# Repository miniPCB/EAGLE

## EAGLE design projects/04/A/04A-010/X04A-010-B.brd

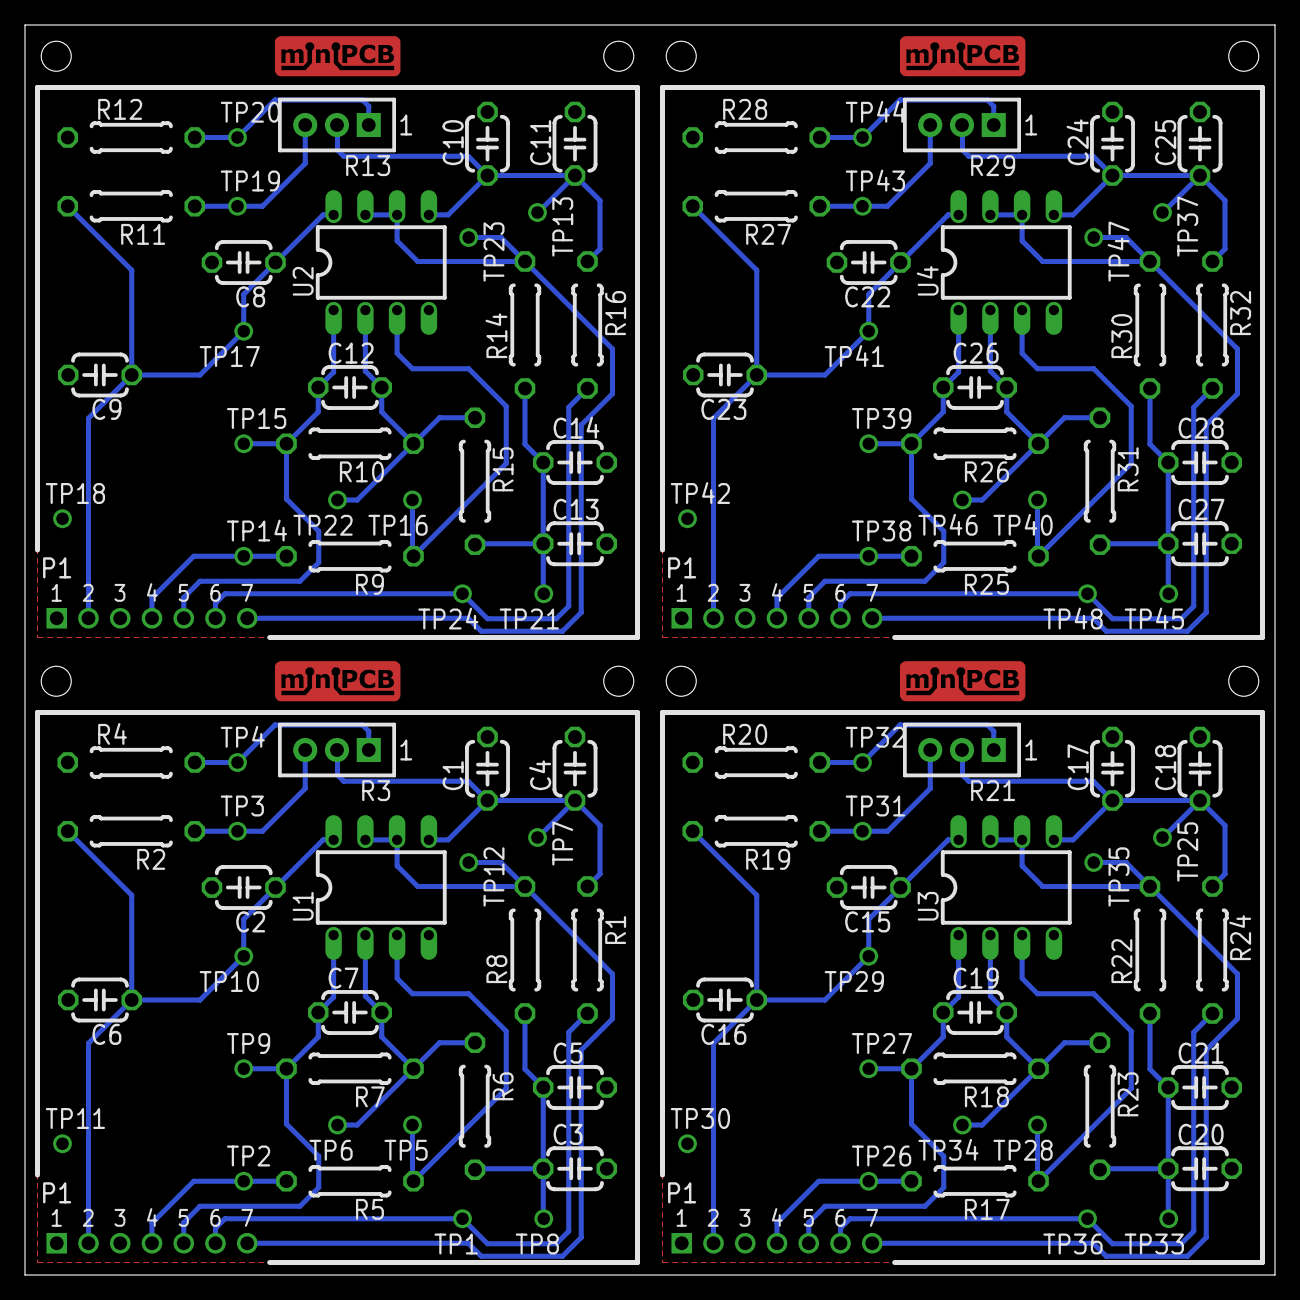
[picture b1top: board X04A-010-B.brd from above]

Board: 2 copper layers, 100.0 x 100.0 mm, 117 parts (0 on the bottom side), 48 nets.

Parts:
C1, C2, C3, C4, C5, C6, C7, C8, C9, C10, C11, C12, C13, C14, C15, C16, C17, C18, C19, C20, C21, C22, C23, C24, C25, C26, C27, C28: C050-024X044
E$1: MINIPCB_PANEL_IMAGEFRAME
P1-, P1-1, P1-2, P1-3: MINIPCB_7P_50X50
R1, R2, R4, R5, R6, R7, R8, R9, R10, R11, R12, R14, R15, R16, R17, R18, R19, R20, R22, R23, R24, R25, R26, R27, R28, R30, R31, R32: 0207/10
R3, R13, R21, R29: TRIM_0100
TP1, TP2, TP3, TP4, TP5, TP6, TP7, TP8, TP9, TP10, TP11, TP12, TP13, TP14, TP15, TP16, TP17, TP18, TP19, TP20, TP21, TP22, TP23, TP24, TP25, TP26, TP27, TP28, TP29, TP30, TP31, TP32, TP33, TP34, TP35, TP36, TP37, TP38, TP39, TP40, TP41, TP42, TP43, TP44, TP45, TP46, TP47, TP48: PINS_1_TESTPOINT_KE5000_NOTEXT
U1, U2, U3, U4: DIL08

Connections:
BIAS: C1.1, C4.1, R1.1, R3.2, TP7.1, U1.5
BIAS1: C10.1, C11.1, R13.2, R16.1, TP13.1, U2.5
BIAS2: C17.1, C18.1, R21.2, R24.1, TP25.1, U3.5
BIAS3: C24.1, C25.1, R29.2, R32.1, TP37.1, U4.5
BIAS_CONTROL: P1-.6, R1.2, TP1.1
BIAS_CONTROL1: P1-1.6, R16.2, TP24.1
BIAS_CONTROL2: P1-2.6, R24.2, TP36.1
BIAS_CONTROL3: P1-3.6, R32.2, TP48.1
GND: C1.2, C2.2, C3.2, C4.2, C5.2, C6.2, P1-.1, R4.1, TP11.1, U1.4
GND1: C8.2, C9.2, C10.2, C11.2, C13.2, C14.2, P1-1.1, R12.1, TP18.1, U2.4
GND2: C15.2, C16.2, C17.2, C18.2, C20.2, C21.2, P1-2.1, R20.1, TP30.1, U3.4
GND3: C22.2, C23.2, C24.2, C25.2, C27.2, C28.2, P1-3.1, R28.1, TP42.1, U4.4
IN: P1-.4, R5.2, TP2.1
IN1: P1-1.4, R9.2, TP14.1
IN2: P1-2.4, R17.2, TP26.1
IN3: P1-3.4, R25.2, TP38.1
IN+: R5.1, TP5.1, U1.3
IN+1: R9.1, TP16.1, U2.3
IN+2: R17.1, TP28.1, U3.3
IN+3: R25.1, TP40.1, U4.3
OUT: C7.1, P1-.5, R7.2, TP9.1, U1.1
OUT1: C12.1, P1-1.5, R10.2, TP15.1, U2.1
OUT2: C19.1, P1-2.5, R18.2, TP27.1, U3.1
OUT3: C26.1, P1-3.5, R26.2, TP39.1, U4.1
POT.1: R3.1, R4.2, TP4.1
POT.2: R11.1, R13.3, TP19.1
POT.3: R2.1, R3.3, TP3.1
POT.4: R12.2, R13.1, TP20.1
POT.5: R19.1, R21.3, TP31.1
POT.6: R20.2, R21.1, TP32.1
POT.7: R27.1, R29.3, TP43.1
POT.8: R28.2, R29.1, TP44.1
V+: C2.1, C6.1, P1-.2, R2.2, TP10.1, U1.8
V+1: C8.1, C9.1, P1-1.2, R11.2, TP17.1, U2.8
V+2: C15.1, C16.1, P1-2.2, R19.2, TP29.1, U3.8
V+3: C22.1, C23.1, P1-3.2, R27.2, TP41.1, U4.8
VFB: C7.2, R6.1, R7.1, TP6.1, U1.2
VFB1: C12.2, R10.1, R15.1, TP22.1, U2.2
VFB2: C19.2, R18.1, R23.1, TP34.1, U3.2
VFB3: C26.2, R26.1, R31.1, TP46.1, U4.2
VREF: P1-.7, R8.2, TP12.1, U1.6, U1.7
VREF1: P1-1.7, R14.2, TP23.1, U2.6, U2.7
VREF2: P1-2.7, R22.2, TP35.1, U3.6, U3.7
VREF3: P1-3.7, R30.2, TP47.1, U4.6, U4.7
VREF_FILTERED: C3.1, C5.1, R6.2, R8.1, TP8.1
VREF_FILTERED1: C13.1, C14.1, R14.1, R15.2, TP21.1
VREF_FILTERED2: C20.1, C21.1, R22.1, R23.2, TP33.1
VREF_FILTERED3: C27.1, C28.1, R30.1, R31.2, TP45.1

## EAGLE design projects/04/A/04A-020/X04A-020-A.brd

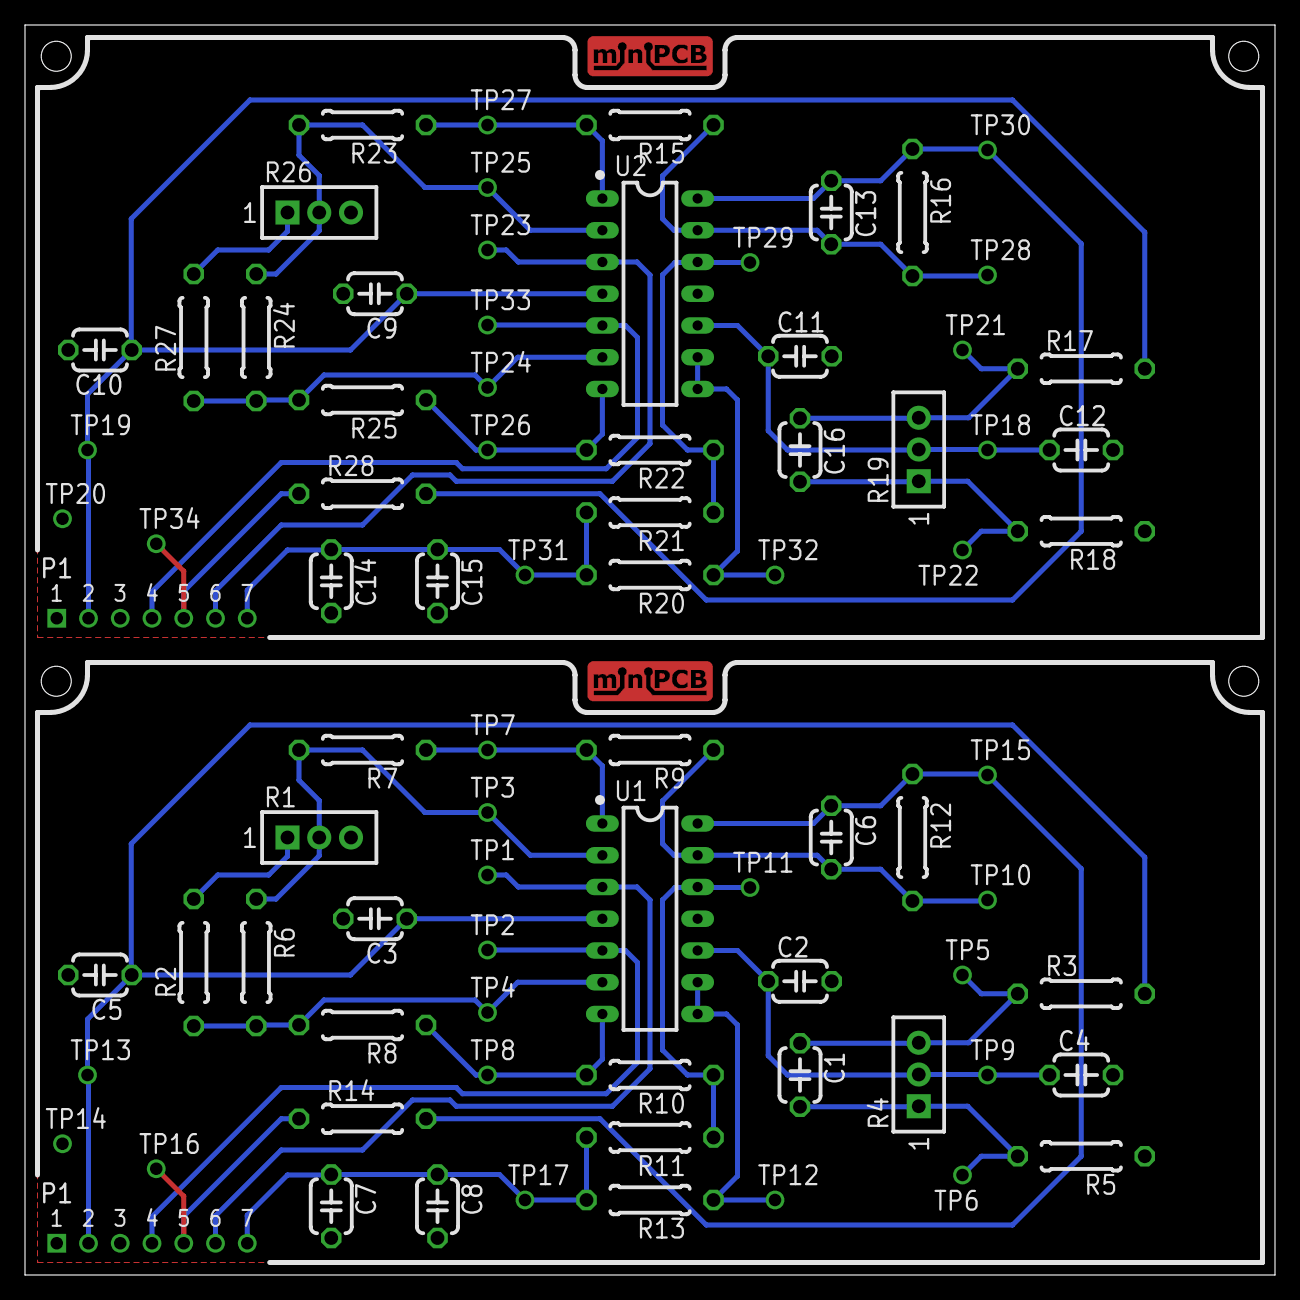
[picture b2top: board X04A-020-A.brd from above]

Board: 2 copper layers, 100.0 x 100.0 mm, 83 parts (0 on the bottom side), 36 nets.

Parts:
C1, C2, C3, C4, C5, C6, C7, C8, C9, C10, C11, C12, C13, C14, C15, C16: C050-024X044
E$1: MINIPCB_PANEL_IMAGEFRAME
P1-, P1-1: MINIPCB_7P_50X100
R1, R4, R19, R26: TRIM_0100
R2, R3, R5, R6, R7, R8, R9, R10, R11, R12, R13, R14, R15, R16, R17, R18, R20, R21, R22, R23, R24, R25, R27, R28: 0207/10
TP1, TP2, TP3, TP4, TP5, TP6, TP7, TP8, TP9, TP10, TP11, TP12, TP13, TP14, TP15, TP16, TP17, TP18, TP19, TP20, TP21, TP22, TP23, TP24, TP25, TP26, TP27, TP28, TP29, TP30, TP31, TP32, TP33, TP34: PINS_1_TESTPOINT_KE5000_NOTEXT
U1, U2: DIL14

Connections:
BIAS: C2.1, C4.1, R4.2, TP9.1, U1.10
BIAS1: C11.1, C12.1, R19.2, TP18.1, U2.10
GND: C2.2, C3.2, C4.2, C5.2, C7.2, C8.2, P1-.1, R5.1, TP14.1, U1.11
GND1: C9.2, C10.2, C11.2, C12.2, C14.2, C15.2, P1-1.1, R18.1, TP20.1, U2.11
unnamed: R10.1, R11.1, TP11.1, U1.12
unnamed: C7.1, C8.1, P1-.7, R11.2, R13.2, TP17.1
unnamed: P1-.4, TP2.1, U1.5
unnamed: P1-.6, TP1.1, U1.3
unnamed: R1.2, R6.1, R7.2, TP3.1, U1.2
unnamed: R2.1, R6.2, R8.2, TP4.1, U1.6
unnamed: R7.1, R9.2, TP7.1, U1.1
unnamed: R8.1, R10.2, TP8.1, U1.7
unnamed: R13.1, TP12.1, U1.8, U1.9
unnamed: R1.1, R2.2
unnamed: P1-.5, R14.1, TP16.1
unnamed: R21.1, R22.1, TP29.1, U2.12
unnamed: C14.1, C15.1, P1-1.7, R20.2, R21.2, TP31.1
unnamed: P1-1.4, TP33.1, U2.5
unnamed: P1-1.6, TP23.1, U2.3
unnamed: R23.2, R24.1, R26.2, TP25.1, U2.2
unnamed: R24.2, R25.2, R27.1, TP24.1, U2.6
unnamed: R15.2, R23.1, TP27.1, U2.1
unnamed: R22.2, R25.1, TP26.1, U2.7
unnamed: R20.1, TP32.1, U2.8, U2.9
unnamed: R26.1, R27.2
unnamed: P1-1.5, R28.1, TP34.1
OUT: C6.1, R12.1, R14.2, TP15.1, U1.14
OUT1: C13.1, R16.1, R28.2, TP30.1, U2.14
POT.1: C1.2, R4.1, R5.2, TP6.1
POT.2: C16.1, R17.1, R19.3, TP21.1
POT.3: C1.1, R3.1, R4.3, TP5.1
POT.4: C16.2, R18.2, R19.1, TP22.1
V+: C3.1, C5.1, P1-.2, R3.2, TP13.1, U1.4
V+1: C9.1, C10.1, P1-1.2, R17.2, TP19.1, U2.4
VFB: C6.2, R9.1, R12.2, TP10.1, U1.13
VFB1: C13.2, R15.1, R16.2, TP28.1, U2.13

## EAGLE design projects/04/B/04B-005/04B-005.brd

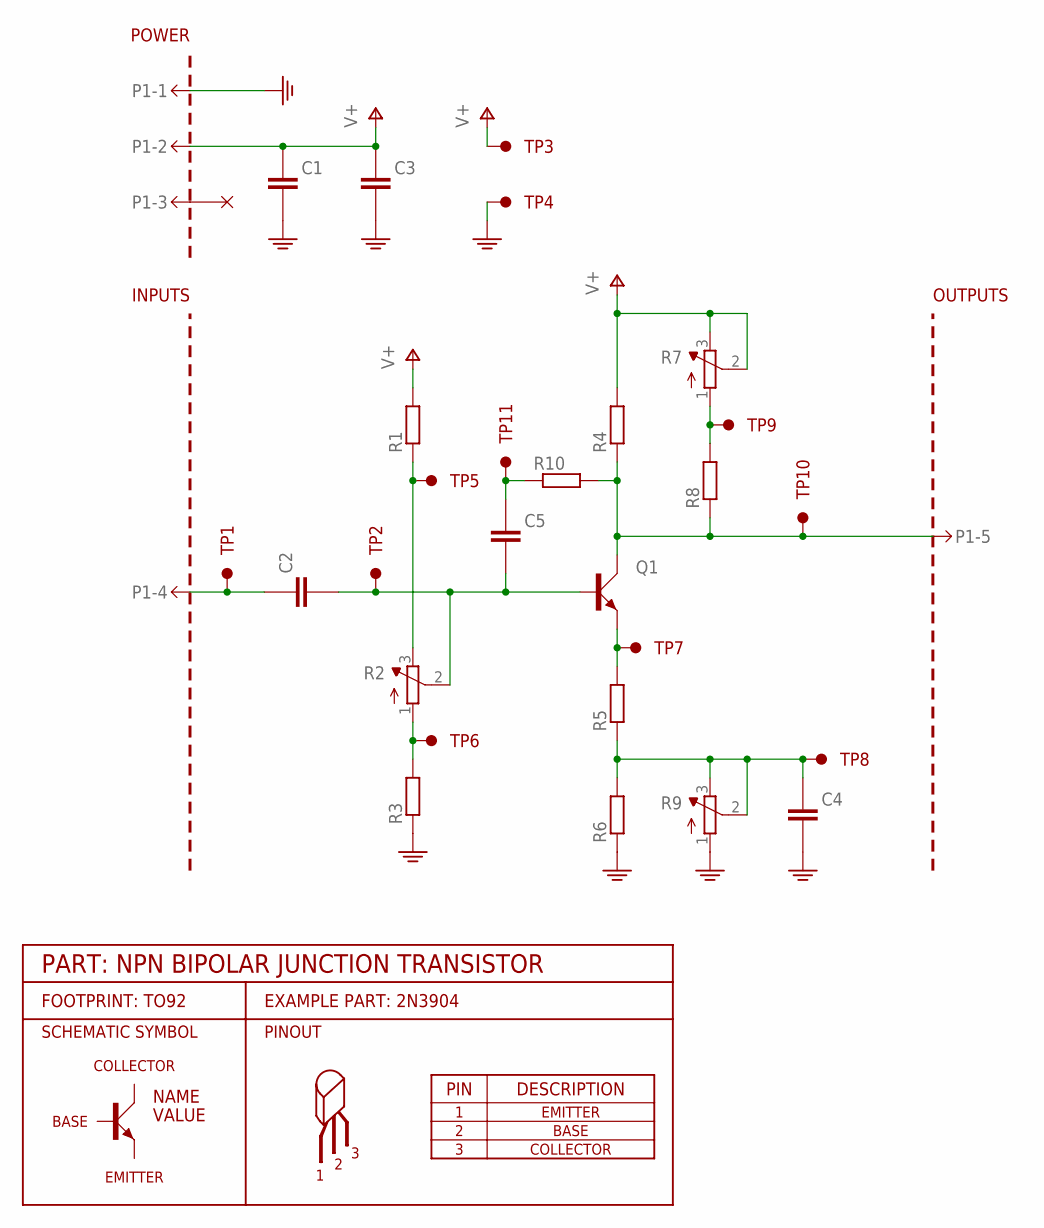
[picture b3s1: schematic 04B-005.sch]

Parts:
C1, C2, C3, C4, C5: CAPACITORTHD; C050-024X044
P1-: MINIPCB_5P50X50; MINIPCB_5P_50X50MM; PART_NUMBER X04B-005-B
Q1: BJT_NPNEBC; TO92-EBC-OVAL
R1, R3, R4, R5, R6, R8, R10: RESISTOR10MM; 0207/10
R2, R7, R9: TRIMPOT0.100THD; TRIM_0100
TP1, TP2, TP3, TP4, TP5, TP6, TP7, TP8, TP9, TP10, TP11: TESTPOINTKE5000-SMTEXT; PINS_1_TESTPOINT_KE5000_NOTEXT

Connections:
GND: C1.2 (-), C3.2 (-), C4.2 (-), P1-.1, R3.1, R6.1, R9.1 (A), TP4.1
unnamed: R7.1 (A), R8.2, TP9.1
unnamed: R1.1, R2.3 (E), TP5.1
unnamed: R2.1 (A), R3.2, TP6.1
unnamed: C4.1 (+), R5.1, R6.2, R9.2 (S), R9.3 (E), TP8.1
unnamed: C2.2 (-), C5.2 (-), Q1.B, R2.2 (S), TP2.1
unnamed: Q1.E, R5.2, TP7.1
unnamed: C5.1 (+), R10.1, TP11.1
unnamed: P1-.5, Q1.C, R4.1, R8.1, R10.2, TP10.1
unnamed: C2.1 (+), P1-.4, TP1.1
V+: C1.1 (+), C3.1 (+), P1-.2, R1.2, R4.2, R7.2 (S), R7.3 (E), TP3.1

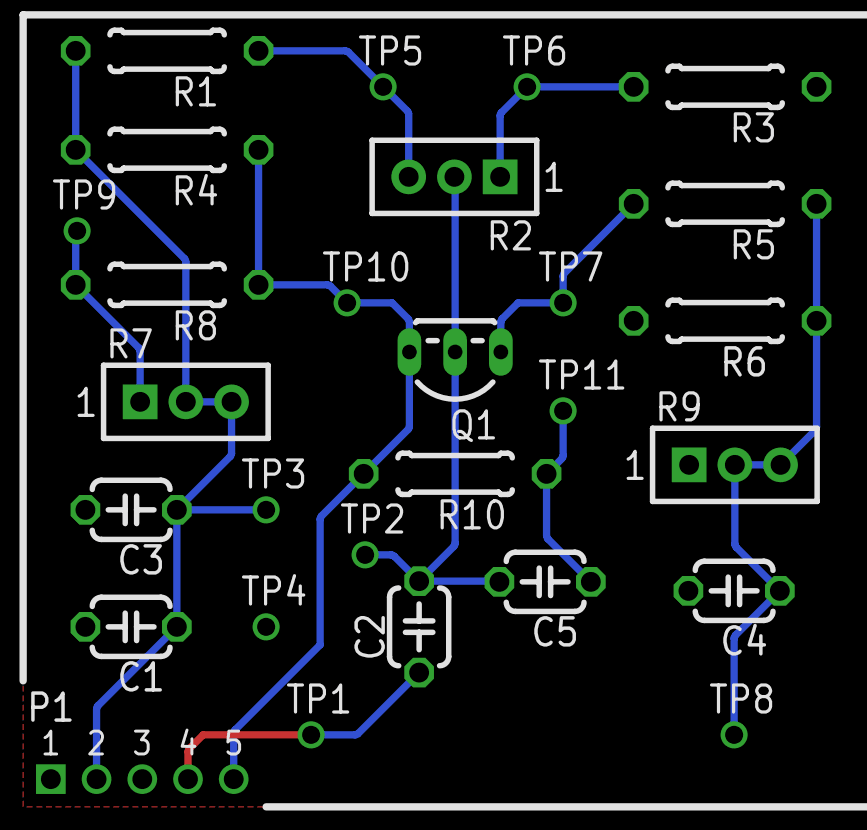
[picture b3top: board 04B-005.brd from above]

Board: 2 copper layers, 28 parts (0 on the bottom side), 11 nets.

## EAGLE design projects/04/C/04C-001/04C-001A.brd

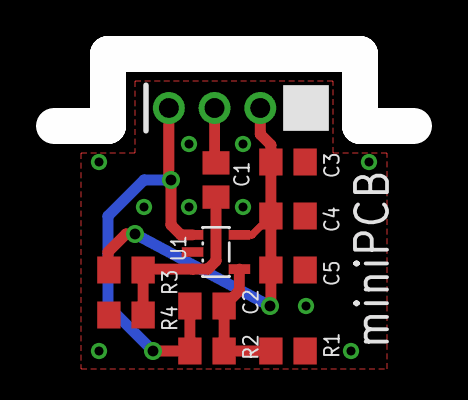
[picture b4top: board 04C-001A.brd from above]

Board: 2 copper layers, 11 parts (0 on the bottom side), 6 nets.

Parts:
C1, C2, C3, C4, C5: C0805
J1: 4-Pin, 0.1" Pitch; PCB_4
R1, R2, R3, R4: R0805
U1: LMH6629/DBV; SOT23-5

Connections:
GND: C3.1, C4.1, C5.1, J1.P$1, R1.1, R4.2, U1.2
IN: C1.1, J1.P$3
unnamed: C1.2, R3.2, R4.1, U1.3
unnamed: C2.2, R1.2, R2.2, U1.4
OUT: C2.1, J1.P$4, R2.1, U1.1
PWR: C3.2, C4.2, C5.2, J1.P$2, R3.1, U1.5

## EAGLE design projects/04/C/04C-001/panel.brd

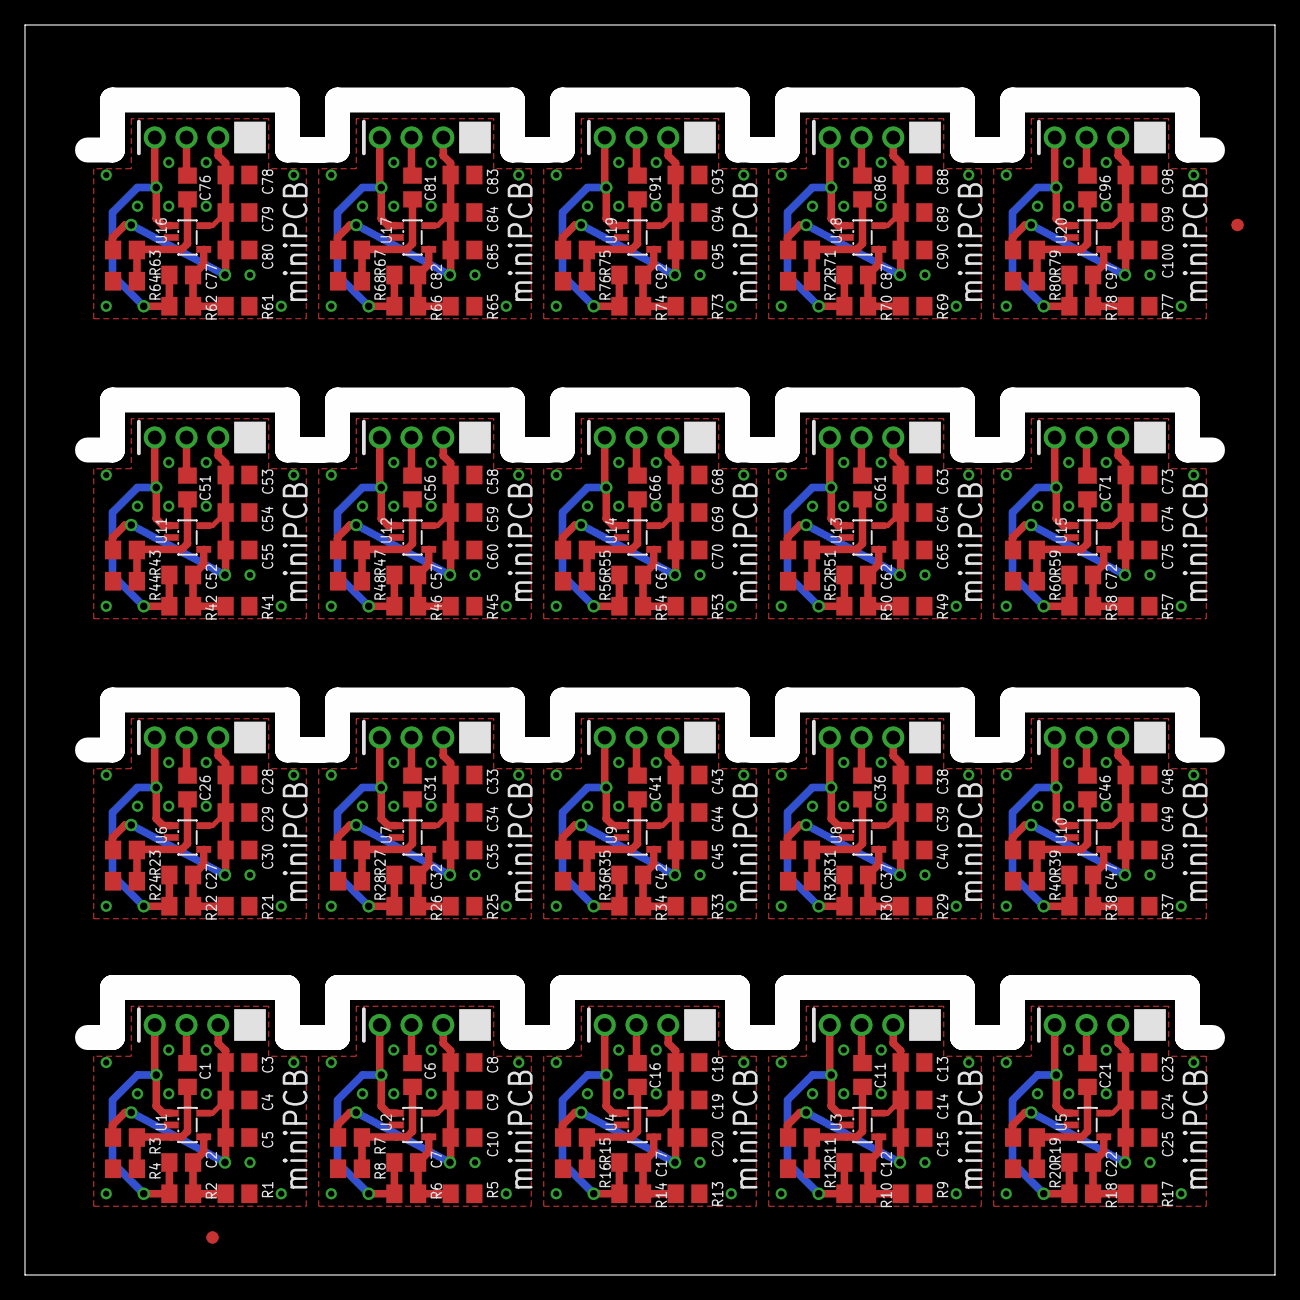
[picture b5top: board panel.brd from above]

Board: 2 copper layers, 100.0 x 100.0 mm, 222 parts (0 on the bottom side), 120 nets.

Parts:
C1, C2, C3, C4, C5, C6, C7, C8, C9, C10, C11, C12, C13, C14, C15, C16, C17, C18, C19, C20, C21, C22, C23, C24, C25, C26, C27, C28, C29, C30, C31, C32, C33, C34, C35, C36, C37, C38, C39, C40, C41, C42, C43, C44, C45, C46, C47, C48, C49, C50, C51, C52, C53, C54, C55, C56, C57, C58, C59, C60, C61, C62, C63, C64, C65, C66, C67, C68, C69, C70, C71, C72, C73, C74, C75, C76, C77, C78, C79, C80, C81, C82, C83, C84, C85, C86, C87, C88, C89, C90, C91, C92, C93, C94, C95, C96, C97, C98, C99, C100: C0805
E$1, E$2: FIDUCIAL
J1, J2, J3, J4, J5, J6, J7, J8, J9, J10, J11, J12, J13, J14, J15, J16, J17, J18, J19, J20: PINS_4SILK; PCB_4
R1, R2, R3, R4, R5, R6, R7, R8, R9, R10, R11, R12, R13, R14, R15, R16, R17, R18, R19, R20, R21, R22, R23, R24, R25, R26, R27, R28, R29, R30, R31, R32, R33, R34, R35, R36, R37, R38, R39, R40, R41, R42, R43, R44, R45, R46, R47, R48, R49, R50, R51, R52, R53, R54, R55, R56, R57, R58, R59, R60, R61, R62, R63, R64, R65, R66, R67, R68, R69, R70, R71, R72, R73, R74, R75, R76, R77, R78, R79, R80: R0805
U1, U2, U3, U4, U5, U6, U7, U8, U9, U10, U11, U12, U13, U14, U15, U16, U17, U18, U19, U20: LMH6629/DBV; SOT23-5

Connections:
GND: C3.1, C4.1, C5.1, J1.P$1, R1.1, R4.2, U1.2
GND1: C8.1, C9.1, C10.1, J2.P$1, R5.1, R8.2, U2.2
GND2: C13.1, C14.1, C15.1, J3.P$1, R9.1, R12.2, U3.2
GND3: C18.1, C19.1, C20.1, J4.P$1, R13.1, R16.2, U4.2
GND4: C23.1, C24.1, C25.1, J5.P$1, R17.1, R20.2, U5.2
GND5: C28.1, C29.1, C30.1, J6.P$1, R21.1, R24.2, U6.2
GND6: C33.1, C34.1, C35.1, J7.P$1, R25.1, R28.2, U7.2
GND7: C38.1, C39.1, C40.1, J8.P$1, R29.1, R32.2, U8.2
GND8: C43.1, C44.1, C45.1, J9.P$1, R33.1, R36.2, U9.2
GND9: C48.1, C49.1, C50.1, J10.P$1, R37.1, R40.2, U10.2
GND10: C53.1, C54.1, C55.1, J11.P$1, R41.1, R44.2, U11.2
GND11: C58.1, C59.1, C60.1, J12.P$1, R45.1, R48.2, U12.2
GND12: C63.1, C64.1, C65.1, J13.P$1, R49.1, R52.2, U13.2
GND13: C68.1, C69.1, C70.1, J14.P$1, R53.1, R56.2, U14.2
GND14: C73.1, C74.1, C75.1, J15.P$1, R57.1, R60.2, U15.2
GND15: C78.1, C79.1, C80.1, J16.P$1, R61.1, R64.2, U16.2
GND16: C83.1, C84.1, C85.1, J17.P$1, R65.1, R68.2, U17.2
GND17: C88.1, C89.1, C90.1, J18.P$1, R69.1, R72.2, U18.2
GND18: C93.1, C94.1, C95.1, J19.P$1, R73.1, R76.2, U19.2
GND19: C98.1, C99.1, C100.1, J20.P$1, R77.1, R80.2, U20.2
IN: C1.1, J1.P$3
IN1: C6.1, J2.P$3
IN2: C11.1, J3.P$3
IN3: C16.1, J4.P$3
IN4: C21.1, J5.P$3
IN5: C26.1, J6.P$3
IN6: C31.1, J7.P$3
IN7: C36.1, J8.P$3
IN8: C41.1, J9.P$3
IN9: C46.1, J10.P$3
IN10: C51.1, J11.P$3
IN11: C56.1, J12.P$3
IN12: C61.1, J13.P$3
IN13: C66.1, J14.P$3
IN14: C71.1, J15.P$3
IN15: C76.1, J16.P$3
IN16: C81.1, J17.P$3
IN17: C86.1, J18.P$3
IN18: C91.1, J19.P$3
IN19: C96.1, J20.P$3
unnamed: C1.2, R3.2, R4.1, U1.3
unnamed: C2.2, R1.2, R2.2, U1.4
unnamed: C6.2, R7.2, R8.1, U2.3
unnamed: C7.2, R5.2, R6.2, U2.4
unnamed: C11.2, R11.2, R12.1, U3.3
unnamed: C12.2, R9.2, R10.2, U3.4
unnamed: C16.2, R15.2, R16.1, U4.3
unnamed: C17.2, R13.2, R14.2, U4.4
unnamed: C21.2, R19.2, R20.1, U5.3
unnamed: C22.2, R17.2, R18.2, U5.4
unnamed: C26.2, R23.2, R24.1, U6.3
unnamed: C27.2, R21.2, R22.2, U6.4
unnamed: C31.2, R27.2, R28.1, U7.3
unnamed: C32.2, R25.2, R26.2, U7.4
unnamed: C36.2, R31.2, R32.1, U8.3
unnamed: C37.2, R29.2, R30.2, U8.4
unnamed: C41.2, R35.2, R36.1, U9.3
unnamed: C42.2, R33.2, R34.2, U9.4
unnamed: C46.2, R39.2, R40.1, U10.3
unnamed: C47.2, R37.2, R38.2, U10.4
unnamed: C51.2, R43.2, R44.1, U11.3
unnamed: C52.2, R41.2, R42.2, U11.4
unnamed: C56.2, R47.2, R48.1, U12.3
unnamed: C57.2, R45.2, R46.2, U12.4
unnamed: C61.2, R51.2, R52.1, U13.3
unnamed: C62.2, R49.2, R50.2, U13.4
unnamed: C66.2, R55.2, R56.1, U14.3
unnamed: C67.2, R53.2, R54.2, U14.4
unnamed: C71.2, R59.2, R60.1, U15.3
unnamed: C72.2, R57.2, R58.2, U15.4
unnamed: C76.2, R63.2, R64.1, U16.3
unnamed: C77.2, R61.2, R62.2, U16.4
unnamed: C81.2, R67.2, R68.1, U17.3
unnamed: C82.2, R65.2, R66.2, U17.4
unnamed: C86.2, R71.2, R72.1, U18.3
unnamed: C87.2, R69.2, R70.2, U18.4
unnamed: C91.2, R75.2, R76.1, U19.3
unnamed: C92.2, R73.2, R74.2, U19.4
unnamed: C96.2, R79.2, R80.1, U20.3
unnamed: C97.2, R77.2, R78.2, U20.4
OUT: C2.1, J1.P$4, R2.1, U1.1
OUT1: C7.1, J2.P$4, R6.1, U2.1
OUT2: C12.1, J3.P$4, R10.1, U3.1
OUT3: C17.1, J4.P$4, R14.1, U4.1
OUT4: C22.1, J5.P$4, R18.1, U5.1
OUT5: C27.1, J6.P$4, R22.1, U6.1
OUT6: C32.1, J7.P$4, R26.1, U7.1
OUT7: C37.1, J8.P$4, R30.1, U8.1
OUT8: C42.1, J9.P$4, R34.1, U9.1
OUT9: C47.1, J10.P$4, R38.1, U10.1
OUT10: C52.1, J11.P$4, R42.1, U11.1
OUT11: C57.1, J12.P$4, R46.1, U12.1
OUT12: C62.1, J13.P$4, R50.1, U13.1
OUT13: C67.1, J14.P$4, R54.1, U14.1
OUT14: C72.1, J15.P$4, R58.1, U15.1
OUT15: C77.1, J16.P$4, R62.1, U16.1
OUT16: C82.1, J17.P$4, R66.1, U17.1
OUT17: C87.1, J18.P$4, R70.1, U18.1
OUT18: C92.1, J19.P$4, R74.1, U19.1
OUT19: C97.1, J20.P$4, R78.1, U20.1
PWR: C3.2, C4.2, C5.2, J1.P$2, R3.1, U1.5
PWR1: C8.2, C9.2, C10.2, J2.P$2, R7.1, U2.5
PWR2: C13.2, C14.2, C15.2, J3.P$2, R11.1, U3.5
PWR3: C18.2, C19.2, C20.2, J4.P$2, R15.1, U4.5
PWR4: C23.2, C24.2, C25.2, J5.P$2, R19.1, U5.5
PWR5: C28.2, C29.2, C30.2, J6.P$2, R23.1, U6.5
PWR6: C33.2, C34.2, C35.2, J7.P$2, R27.1, U7.5
PWR7: C38.2, C39.2, C40.2, J8.P$2, R31.1, U8.5
PWR8: C43.2, C44.2, C45.2, J9.P$2, R35.1, U9.5
PWR9: C48.2, C49.2, C50.2, J10.P$2, R39.1, U10.5
PWR10: C53.2, C54.2, C55.2, J11.P$2, R43.1, U11.5
PWR11: C58.2, C59.2, C60.2, J12.P$2, R47.1, U12.5
PWR12: C63.2, C64.2, C65.2, J13.P$2, R51.1, U13.5
PWR13: C68.2, C69.2, C70.2, J14.P$2, R55.1, U14.5
PWR14: C73.2, C74.2, C75.2, J15.P$2, R59.1, U15.5
PWR15: C78.2, C79.2, C80.2, J16.P$2, R63.1, U16.5
PWR16: C83.2, C84.2, C85.2, J17.P$2, R67.1, U17.5
PWR17: C88.2, C89.2, C90.2, J18.P$2, R71.1, U18.5
PWR18: C93.2, C94.2, C95.2, J19.P$2, R75.1, U19.5
PWR19: C98.2, C99.2, C100.2, J20.P$2, R79.1, U20.5

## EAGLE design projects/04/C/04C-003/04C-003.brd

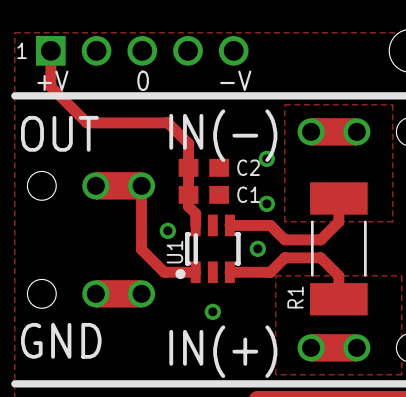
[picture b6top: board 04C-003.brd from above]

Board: 2 copper layers, 9 parts (0 on the bottom side), 5 nets.

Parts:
04C-003: Current Sense Amp; MINIPCB_25X25MM
C1: 4n7; C0603
C2: 4u7; C0603
P1: IN+; PINS_1_1MM_K
P2: IN-; PINS_1_1MM_K
P3: GND; PINS_1_1MM_K
P4: OUT; PINS_1_1MM_K
R1: R2512K
U1: INAX81; SOT23-6

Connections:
GND: 04C-003.3, C1.2, C2.2, P3.1, P3.2, U1.2, U1.5
IN+: P1.1, P1.2, R1.1, U1.3
IN-: P2.1, P2.2, R1.2, U1.4
unnamed: P4.1, P4.2, U1.1
unnamed: 04C-003.1, C1.1, C2.1, U1.6

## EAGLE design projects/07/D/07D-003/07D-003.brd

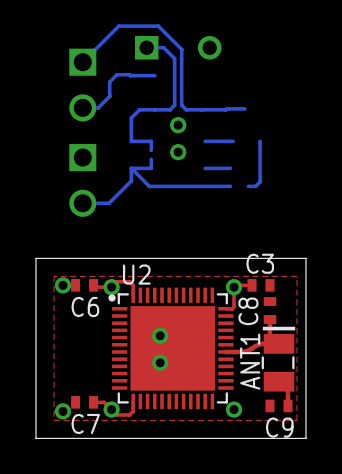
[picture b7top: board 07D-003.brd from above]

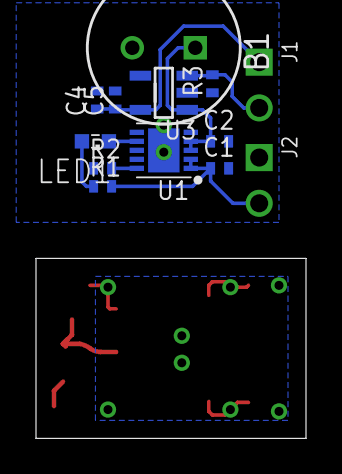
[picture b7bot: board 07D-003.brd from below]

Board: 6 copper layers, 15.0 x 10.0 mm, 20 parts (13 on the bottom side), 10 nets.

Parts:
ANT1: M310220
B1: SLB08115L140; BATTERY_SLB08115L140
C1, C2, C5: 1u; C0402
C3, C6, C7: 100n; C0402
C4: 10n; C0402
C8: 4p7; C0402
C9: 2p7; C0402
J1: ON/OFF JUMPER; PINS_2
J2: POWER; PINS_2
LED1: SML0603
R1: 150; R0402
R2: 4k99; R0402
R3: 499k; R0402
U1: MCP73113-16SI/MF; DFN-10
U2: NRF52832-QFAA-R7; QFN40P600X600X90-49N
U3: ADP150AUJZ-3.3-R7; SOT25

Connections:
+3V3: C3.1, C4.1, C5.1, C6.1, C7.1, J1.1, U2.13, U2.36, U2.48, U3.5
ANTFEED: ANT1.1, C8.1, U2.30
ANTGND: ANT1.2, C9.1
B+: B1.1+, C2.1, U1.3, U1.4, U3.1
ENABLE: J1.2, R3.2, U3.3
GND: B1.2-, C1.2, C2.2, C3.2, C4.2, C5.2, C6.2, C7.2, C8.2, C9.2, J2.1, R2.1, R3.1, U1.8, U1.9, U1.EP, U2.31, U2.45, U2.49, U3.2
LED+: LED1.A, R1.1
PROG: R2.2, U1.10
STAT: LED1.C, U1.7
V+: C1.1, J2.2, R1.2, U1.1, U1.2
